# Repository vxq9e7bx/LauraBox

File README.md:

# LauraBox
A children's juke box controlled by RFID tags, based on an ESP32.

## Features:
* Playback of user-defined MP3 playlists
* Playlist selected though RFID tag. Cheap RFID stickers can be placed on any 3D printed model.
* Battery powered, can play while charging
* Four buttons: volume +/-, next/previous track
* Intuitive pause functionality by removing the RFID tag and putting it back on to resume (no limit in pause time, no impact on battery life)
* WiFi download of new MP3s and playlists
* Firmware upgrade via WiFi
* Long standby time (several month)
* Long play time (many hours, if not days)
* Toddler proof :-)

## Main components
* EPS32 microcontroller
* MFRC522 RFID board
* PCM5102 I2S stereo audio DAC
* PAM8403 stereo amplifier
* Pair of wideband speakers
* 3.6V Li-ion battery with USB charge controller from a USB power bank (2x 18650-type cells with 2500 mAh)
* SD card to store MP3 files and playlists

## Why use the ESP32?

At first I was considering building the box based on a Raspberry Pi. I had an old first generation Pi lying around unused, so I though it would be a good way of using it. I was immediately disappointed by its sound quality. Although this is significantly better on newer models, I learned another lession: The power consumption of a Raspberry Pi is very high, and it takes a long time to boot. Keeping it always running to wait for an RFID card to be detected is out of the question, since I wanted it to run from battery. Adding a small microcontroller (I though of some ATMega) to switch on the Pi only when a card is detected would result in long wait times until the music starts playing. Also the power consumption while playing would be still quite high. A Raspberry Pi typically uses 300 to 500 mA, while an ESP32 just takes a few mA when WiFi is disabled. After short investigation I found the ESP32-audioI2S Arduino library. This makes playback of audio using an ESP32 super easy. Thanks to the ultra low power co-processor of the ESP32 it is possible to cut down the power consumption in sleep mode to around 0.5mA-1.0mA on average (incl. periodic wakeups and RFID reads), which gives you plenty of standby time on battery.

## Power supply

For power supply I have used an old USB power bank which I no longer needed. It has two 18650-typed cells with each 2500 mAh and a USB charge controller with an integrated boost converted to generate 5V from the ~3.6 V battery voltage (the cells are in parallel). The 5V USB voltage is not usable to power a very low power device, since the boost converter switches off if too little current is drawn. Since the electronics anyways runs on 3.3 V, the battery voltage is used without the boost converter directly. Since the voltage can be as high as 4 V or even higher when the battery is fully chaged, and the ESP32 has a maximum voltage of 3.6 V, a voltage regulator is required. I have decided for a MaxLinear XRP6272, since it has a very low quiescent current, a quite low dropout voltage and is able to provide a high enough current so that WiFi will work without problems.

The PCM5102 has unfortunately a relatively high quiescent current, hence I decided to use two XRP6272: one for the ESP32, the MRF522 and the SD card, the second formt the PCM5102. The first regulator is permanently enabled, since the ESP32 needs permanent power, and both the SD card and the MRF522 can be powered down to a sufficiently low quiescent current. Only the second regulator is controlled by software.

The PAM8403 is directly connected to the battery voltage, since it is favourable to power it with the highest possible voltage (up to 5V). I have experimented with using the 5V USB power as a supply, but it draws too little current to switch it on. Luckily, the power down mode of the PAM8403 is also sufficiently low, so no extra switch is required here.

It is a bit difficult to measure the power consumption in standby mode precisely, because it switches between deep-sleep modes and very short bursts of RFID-activity (with only the ULP processor working in the ESP32). The average current seems to be around 1mA. Since the battery cannot be used to its full capacity, because the voltage is getting too low at some point, the lifetime is a bit below the theoretical 5000hours = 208days. Even if it were only half of that, it would be still nothing to worry about too much.

Also to get down the power consumption, I have removed the LED from the MFRC522 board. It was always on even while the MFRC522 was put to standby and hence was unnecessarily drawing a significant amount of power.

## Firmware

The firmware is based on Arduino and uses the following libraries:
* ESP32 I2S audio library: https://github.com/schreibfaul1/ESP32-audioI2S
* ArduinoOTA (from Arduino library manager)
* ArduinoHttpClient (from Arduino library manager)

It also uses the ulptool (https://github.com/duff2013/ulptool) to program the ULP (ultra low power co-processor) of the ESP32.

Please have a look at the header of the Arduino sketch for instructions how to build the firmware. You will also have to create the `wifi-key.h` header file containing your WiFi credentials and the URL to download MP3 and playlists from (see section "Server setup for playlists and MP3 files"):
```
// Create wifi-key.h, put the following two definitions in and replace the **** with your WIFI credentials.
String ssid =     "****";
String password = "****";
String updateCard = <cardIdToActivateWifiUpload>;
String baseUrl = "http://url.to.download.new.card.content"
```

The `<cardIdToActivateWifiUpload>` is the RFID card id (as an integer, prefix with `0x` for hex format) which will trigger entering the WiFi firmware update and playlist/MP3 download mode.

### Usage of the ULP

The ULP periodically queries the status of the RFID card, wakes the main CPU if a new card is detected, and informs the main CPU of the current card ID and when the card is lost. Writing this code was the actual fun part of the firmware development for this project. The ULP is a very minimalistic CPU, there isn't even a (complete) C compiler (I wasn't able to get the experimental ULPCC compiler to work at all). So I had to write assembler code. There are only very few registers. The CPU doesn't even have a stack, but you can implement one (see `stack.s`). Since the ULP does not have access to the peripherals (they are powered down anyway), the SPI communication with the MRFC522 has to be bit-banged through normal GPIO pins. To get this right, I have basically observed the communication of a normal Arduino program using an MRFC522 library with a logic analyzer. Then I have basically coded the same sequence of bytes into the ULP program (see `init_sequence` section in `rtcio.s`). The only goal was to read the ID of the card, which is luckily not so hard to achieve. Even though some error checking is missing, the communication seems to be pretty reliably.

Since the ULP can also run when the main CPU is active, it will keep monitoring the presence of the RFID card and inform the main CPU when it is lost. The main CPU will then shutdown. An interesting fact about the ESP32 is also that the main CPU will be completely shutoff while in deep sleep mode, so when the ULP wakes it, it will boot the program from the very beginning (i.e. it will go through `setup()` again). Only by looking at the wakeup cause it is possible to distinguish this from a cold boot. All memory content (apart from the ULP accessible memory) will be lost, too. For this particular purpose this is perfectly fine, since the box does not need to store big amount of data while sleeping. Only the current volume setting and the last playback position is stored in the ULP memory.

## Electronics

* Analogue part is well-separated from digital part, to avoid any influence of RFID or WiFi operation on sound quality.
* This works well, there is no audible noise from RFID or WiFi.

### Possible improvements:

* Some things may be a bit cheated: digital signals (I2S etc.) going to the analogue side should better be decoupled with opto-couplers, because ground levels might be different. It seems to work well like it is, though.
* Some components (choke, analogue supply bypass capacitor) are quite overdimensioned, just to be on the safe side.
  * I did that to avoid the risk of needing a second order with only a few parts, if I would estimate wrongly...
* Placement of some components was not smart:
  * The serial programming connector was originally planned as an upright connector, so it can be reached while the board is inside the box. This collided with the RFID board, so I changed it to an angled connector. This is a bit unhandy, because it requires taking the board out when using it. Also no big deal, since there is WiFi firmware upgarade...
  * Some bigger components, especially the choce, are placed a bit too close to the edge, which makes assembly a bit hard.
* Keep the area below the WiFi antenna free (no ground, no signals). This is hard to achieve with a home-produced board with just two layers, but at least one could move the signals as close as possible to the edge of the area and remove the ground plane there, ideally with a real cut out in the board.
* I am not an electronics engineer, surely one can do a number of other things better, too!

## Mechanical parts

* The outer parts are made from plywood with a CNC mill.
  * Don't look to close at my work. This was the first time for me do build such a case with my CNC mill, which is more like a 3D printer that can also mill...
* The buttons are also made from wood, which creates a uniform look. The reset button can be triggered with a paper clip.
* The wood is finished with wood wax.
* The holder for the battery and the charge controller are 3D printed.
* The corners holding the electronics have nuts glued in from the bottom.
* Spacers are required between the electronics and the top lid of the casing.
* Speakers are secured with screws and nuts. To simplify the assembly, I have glued the nuts to the speakers.

### Possible improvements:

* The drilled holes for the sound to exit the box are too small, this degrades sound quality a bit unfortunately.
* Assembly is slightly tedious due to the spacers between electronics and the lid, but thanks to Wifi connectivity this needs not be done often.
* Also the box is a bit too small for the electronics board (or the board is to big). I had to grind some material off the walls on the inside to make it fit.

## Server setup for playlists and MP3 files

* A web server needs to be setup which provides playlists and MP3 files
* The web server needs to be reachable by the box when connected to the WiFi defined in `wifi-key.h` through the specified URI.
  * It is strongly recommended to restrict access to the web server to your local network or even just the IP address of the box, to avoid exposing copyrighted material to the internet.
* When detecting the special `updateCard`, the firmware will download a file called `0.lst.manifest`, which contains a list of file sizes and names (one entry per line).
* It will then check each entry whether the file exists on the SD card and its size matches. Any missing or wrong-sized file will be downloaded. Any extra file will be deleted.
* Playlists need to be named after the card ID which should activate the play back of the list: `<cardId>.lst` (e.g. `deadbeef.lst` if `deadbeef` is a card id). They simply contain a plain list of MP3 files which should be played back in sequence. The playlist file and all MP3s need to be in the manifest file, so they are properly downloaded.
* During playback, there normally is no WiFi connection to safe power. It is possible though to have web radio streams in the playlists. If a playlist entry starts with `http://`, WiFi will be activated before the stream is started. Note that this will work only with MP3-based streams, and it will reduce the battery life considerably.
* To generate a playlist on a Linux system, use the script `scripts/makeList.sh`.
* To generate or update the manifest, use the script `scripts/makeManifest.sh`.
* Do not use non-ASCII characters in file names. Use the script `scripts/fileRenamer.sh` to rename files such that those characters are avoided.
* To correct the sound distortions caused by the small holes in the casing letting, I use the script `scripts/soundCorrection.sh`. I would recommend rather making those holes bigger, but if you face similar issues this can be helpful.
* If you have a Youtube Music account and want to download MP3 files from there to the box, have a look at the scripts `scripts/ytmSetup.py` and `scripts/ytmLoader.py` and modify them for your needs.

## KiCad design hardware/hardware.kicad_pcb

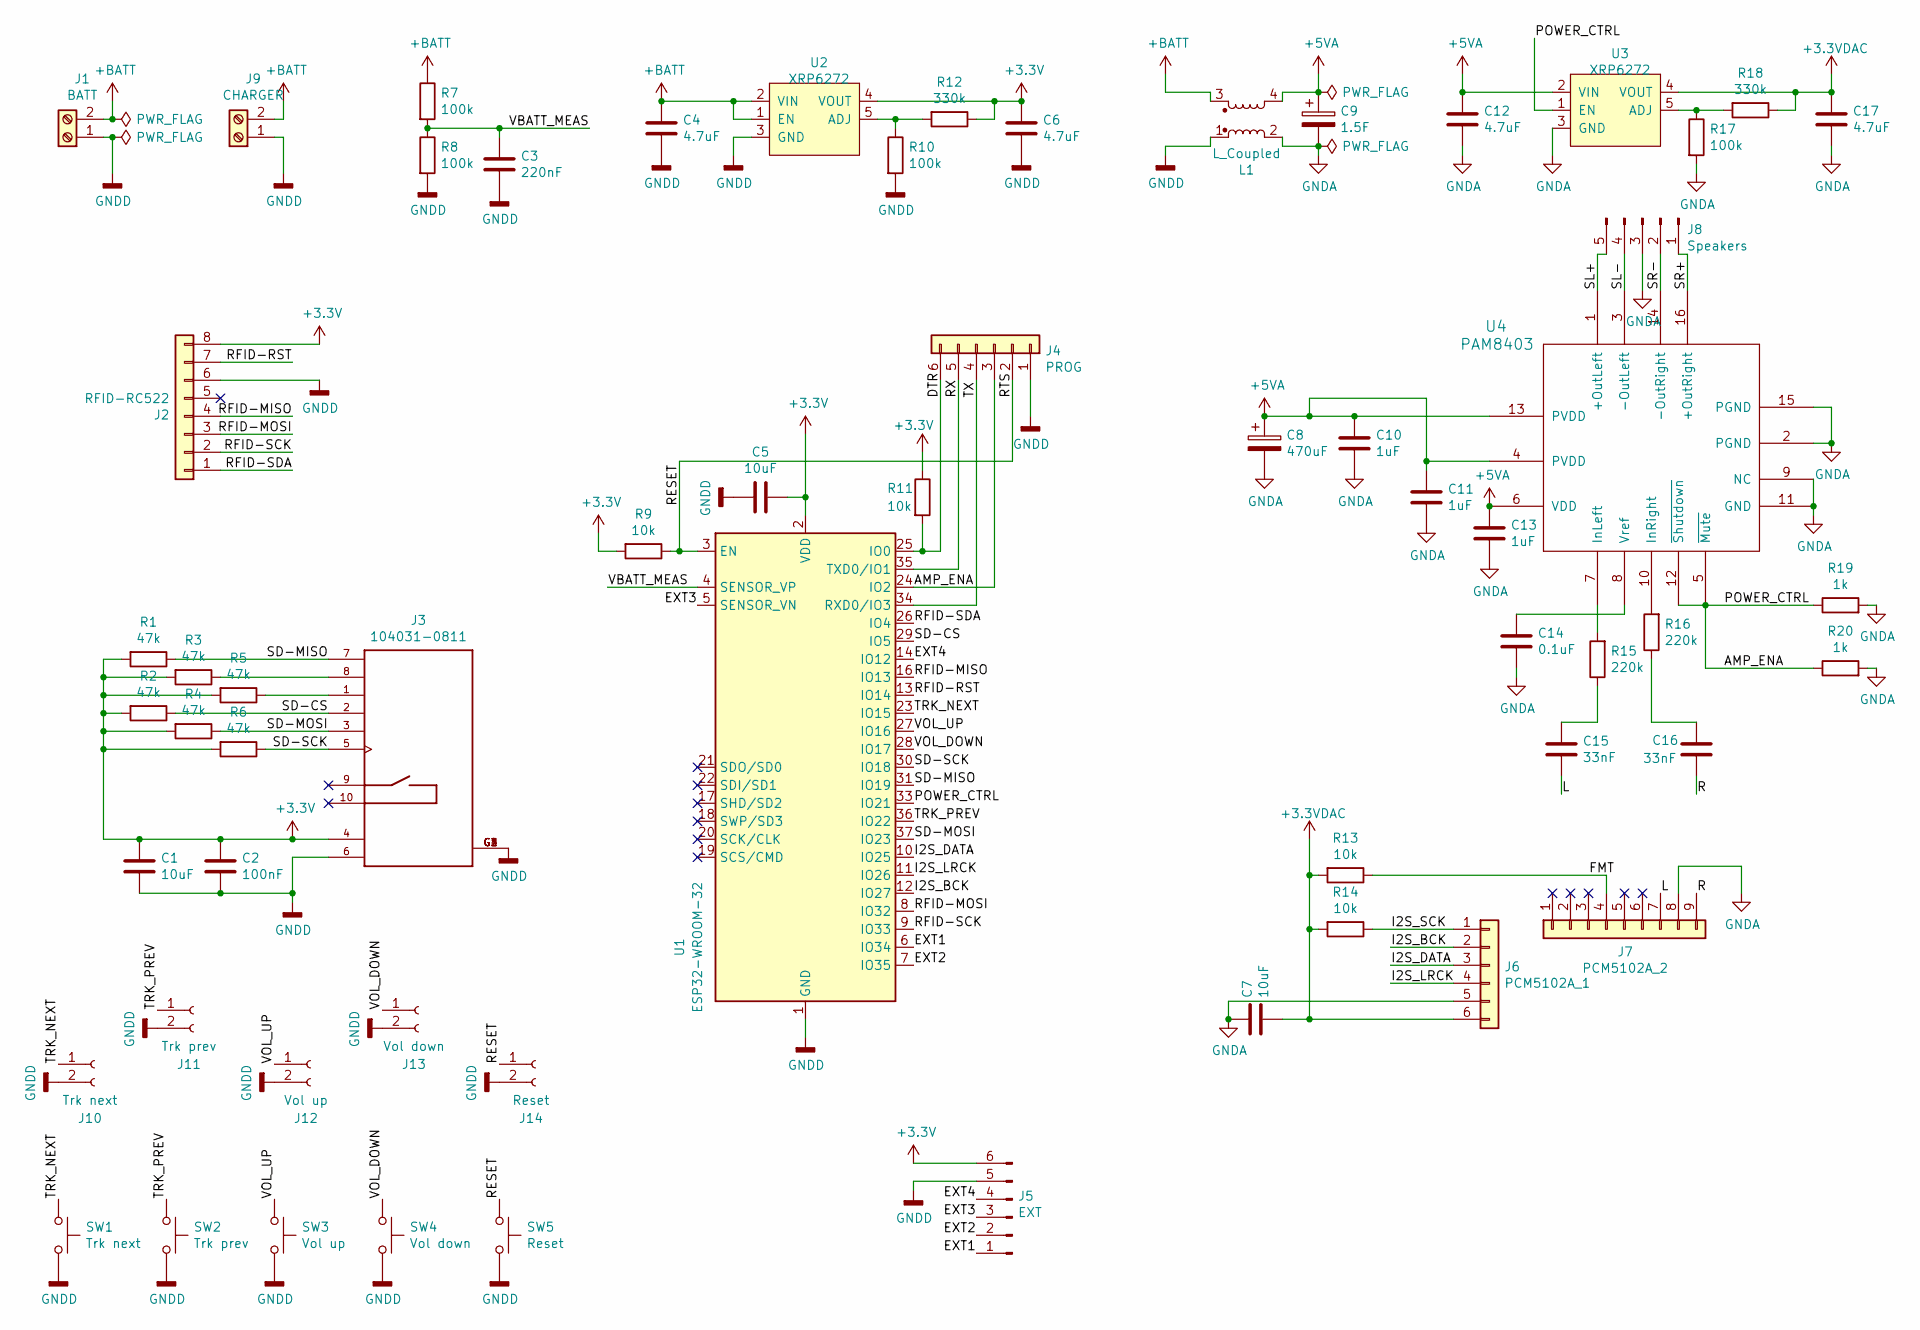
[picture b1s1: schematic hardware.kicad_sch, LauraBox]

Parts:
C1, C5, C7: 10uF; C_0805_2012Metric_Pad1.15x1.40mm_HandSolder
C2: 100nF; C_Disc_D3.0mm_W1.6mm_P2.50mm
C3: 220nF; C_Disc_D3.0mm_W1.6mm_P2.50mm
C4, C6, C12, C17: 4.7uF; C_1206_3216Metric_Pad1.42x1.75mm_HandSolder
C8: 470uF; CP_Radial_D8.0mm_P3.80mm
C9: 1.5F; C_Rect_L16.5mm_W8.7mm_P15.00mm_MKT
C10, C11, C13: 1uF; C_Rect_L4.6mm_W5.5mm_P2.50mm_MKS02_FKP02
C14: 0.1uF; C_Disc_D3.0mm_W1.6mm_P2.50mm
C15, C16: 33nF; C_Disc_D3.0mm_W1.6mm_P2.50mm
J1: BATT; Molex_KK-254_AE-6410-02A_1x02_P2.54mm_Vertical
J2: RFID-RC522; RFID-RC522-Module
J3: 104031-0811; 1040310811
J4: PROG; Molex_KK-254_AE-6410-06A_1x06_P2.54mm_Vertical
J5: EXT; PinHeader_2x03_P2.54mm_Vertical
J6: PCM5102A_1; PinSocket_1x06_P2.54mm_Vertical
J7: PCM5102A_2; PinSocket_1x09_P2.54mm_Vertical
J8: Speakers; Molex_KK-254_AE-6410-05A_1x05_P2.54mm_Vertical
J9: CHARGER; Molex_KK-254_AE-6410-02A_1x02_P2.54mm_Vertical
J10: Trk next; PinHeader_1x02_P2.54mm_Vertical
J11: Trk prev; PinHeader_1x02_P2.54mm_Vertical
J12: Vol up; PinHeader_1x02_P2.54mm_Vertical
J13: Vol down; PinHeader_1x02_P2.54mm_Vertical
J14: Reset; PinHeader_1x02_P2.54mm_Vertical
L1: L_Coupled; Choke_21x17mm
R1, R2, R3, R4, R5, R6: 47k; R_0612_1632Metric_Pad1.18x3.40mm_HandSolder
R7, R8, R10, R17: 100k; R_0612_1632Metric_Pad1.18x3.40mm_HandSolder
R9, R11, R13, R14: 10k; R_0612_1632Metric_Pad1.18x3.40mm_HandSolder
R12, R18: 330k; R_0612_1632Metric_Pad1.18x3.40mm_HandSolder
R15, R16: 220k; R_0612_1632Metric_Pad1.18x3.40mm_HandSolder
R19, R20: 1k; R_0612_1632Metric_Pad1.18x3.40mm_HandSolder
SW1: Trk next; SW_Push_1P1T_NO_6x6mm_H9.5mm
SW2: Trk prev; SW_Push_1P1T_NO_6x6mm_H9.5mm
SW3: Vol up; SW_Push_1P1T_NO_6x6mm_H9.5mm
SW4: Vol down; SW_Push_1P1T_NO_6x6mm_H9.5mm
SW5: Reset; SW_Push_1P1T_NO_6x6mm_H9.5mm
U1: ESP32-WROOM-32
U2, U3: XRP6272; TO-252-5_TabPin3
U4: PAM8403; SOP-16_4.55x10.3mm_P1.27mm

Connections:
+3.3VDAC: C7.2, C17.1, J6.6, R13.2, R14.2, R18.1, U3.4 (VOUT)
+3V3: C1.1, C2.1, C5.1, C6.1, J2.8, J3.4 (VDD), J5.6, R1.2, R2.2, R3.2, R4.2, R5.2, R6.2, R9.2, R11.1, R12.1, U1.2 (VDD), U2.4 (VOUT)
+5VA: C8.1, C9.1, C10.1, C11.1, C12.1, C13.1, L1.4, U3.2 (VIN), U4.4 (PVDD), U4.6 (VDD), U4.13 (PVDD)
+BATT: C4.1, J1.2, J9.2, L1.3, R7.1, U2.1 (EN), U2.2 (VIN)
/AMP_ENA: J4.3, R19.1, R20.1, U1.24 (IO2), U1.33 (IO21), U3.1 (EN), U4.5 (~Mute), U4.12 (~Shutdown)
/DTR: J4.6, R11.2, U1.25 (IO0)
/EXT1: J5.1, U1.6 (IO34)
/EXT2: J5.2, U1.7 (IO35)
/EXT3: J5.3, U1.5 (SENSOR_VN)
/EXT4: J5.4, U1.14 (IO12)
/FMT: J7.4, R13.1
/I2S_BCK: J6.2, U1.12 (IO27)
/I2S_DATA: J6.3, U1.10 (IO25)
/I2S_LRCK: J6.4, U1.11 (IO26)
/I2S_SCK: J6.1, R14.1
/L: C15.2, J7.7
/R: C16.1, J7.9
/RESET: J4.2, J14.1, R9.1, SW5.1, U1.3 (EN)
/RFID-MISO: J2.4, U1.16 (IO13)
/RFID-MOSI: J2.3, U1.8 (IO32)
/RFID-RST: J2.7, U1.13 (IO14)
/RFID-SCK: J2.2, U1.9 (IO33)
/RFID-SDA: J2.1, U1.26 (IO4)
/RX: J4.5, U1.35 (TXD0/IO1)
/SD-CS: J3.2 (CD/DAT3), R2.1, U1.29 (IO5)
/SD-MISO: J3.7 (DAT0), R1.1, U1.31 (IO19)
/SD-MOSI: J3.3 (CMD), R4.1, U1.37 (IO23)
/SD-SCK: J3.5 (CLK), R6.1, U1.30 (IO18)
/SL+: J8.5, U4.1 (+OutLeft)
/SL-: J8.4, U4.3 (-OutLeft)
/SR+: J8.1, U4.16 (+OutRight)
/SR-: J8.2, U4.14 (-OutRight)
/TRK_NEXT: J10.1, SW1.1, U1.23 (IO15)
/TRK_PREV: J11.1, SW2.1, U1.36 (IO22)
/TX: J4.4, U1.34 (RXD0/IO3)
/VBATT_MEAS: C3.1, R7.2, R8.1, U1.4 (SENSOR_VP)
/VOL_DOWN: J13.1, SW4.1, U1.28 (IO17)
/VOL_UP: J12.1, SW3.1, U1.27 (IO16)
GNDA: C7.1, C8.2, C9.2, C10.2, C11.2, C12.2, C13.2, C14.1, C17.2, J6.5, J7.8, J8.3, L1.2, R17.2, R19.2, R20.2, U3.3 (GND), U4.2 (PGND), U4.9 (NC), U4.11 (GND), U4.15 (PGND)
GNDD: C1.2, C2.2, C3.2, C4.2, C5.2, C6.2, J1.1, J2.6, J3.6 (VSS), J3.G1 (GND), J3.G2 (GND), J3.G3 (GND), J3.G4 (GND), J4.1, J5.5, J9.1, J10.2, J11.2, J12.2, J13.2, J14.2, L1.1, R8.2, R10.2, SW1.2, SW2.2, SW3.2, SW4.2, SW5.2, U1.1 (GND), U1.15 (GND), U1.38 (GND), U1.39 (GND), U2.3 (GND)
unnamed: C14.2, U4.8 (Vref)
unnamed: C15.1, R15.1
unnamed: C16.2, R16.1
unnamed: J3.1 (DAT2), R5.1
unnamed: J3.8 (DAT1), R3.1
unnamed: R10.1, R12.2, U2.5 (ADJ)
unnamed: R15.2, U4.7 (InLeft)
unnamed: R16.2, U4.10 (InRight)
unnamed: R17.1, R18.2, U3.5 (ADJ)

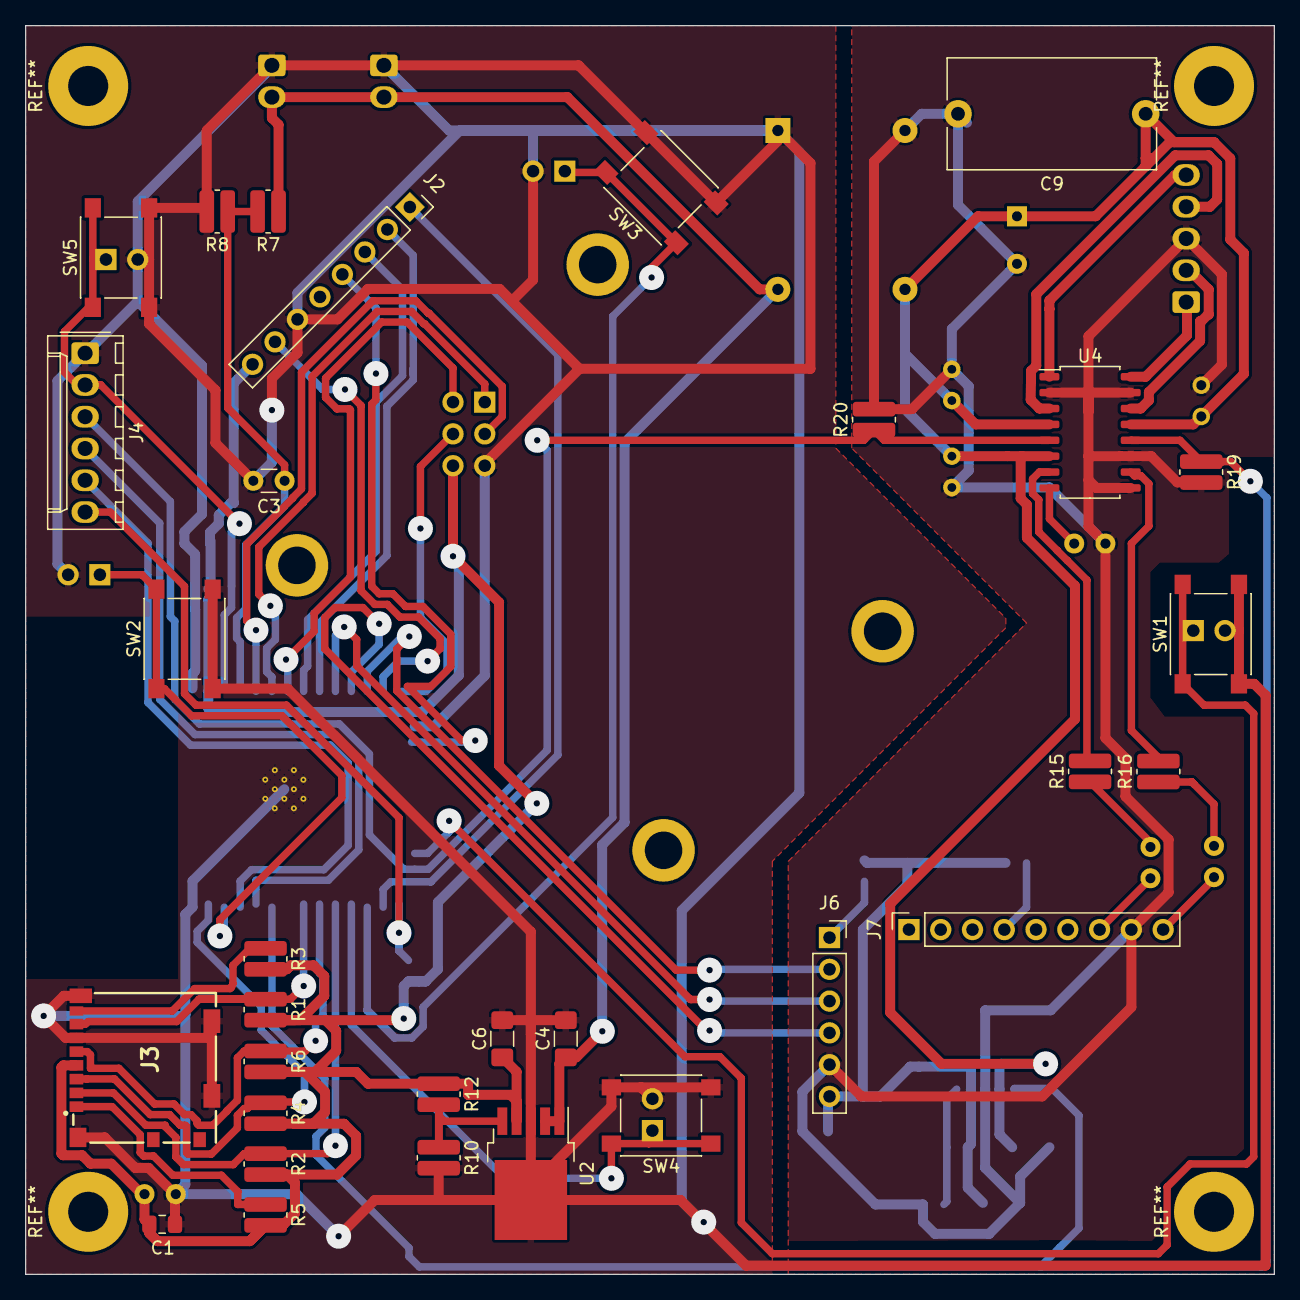
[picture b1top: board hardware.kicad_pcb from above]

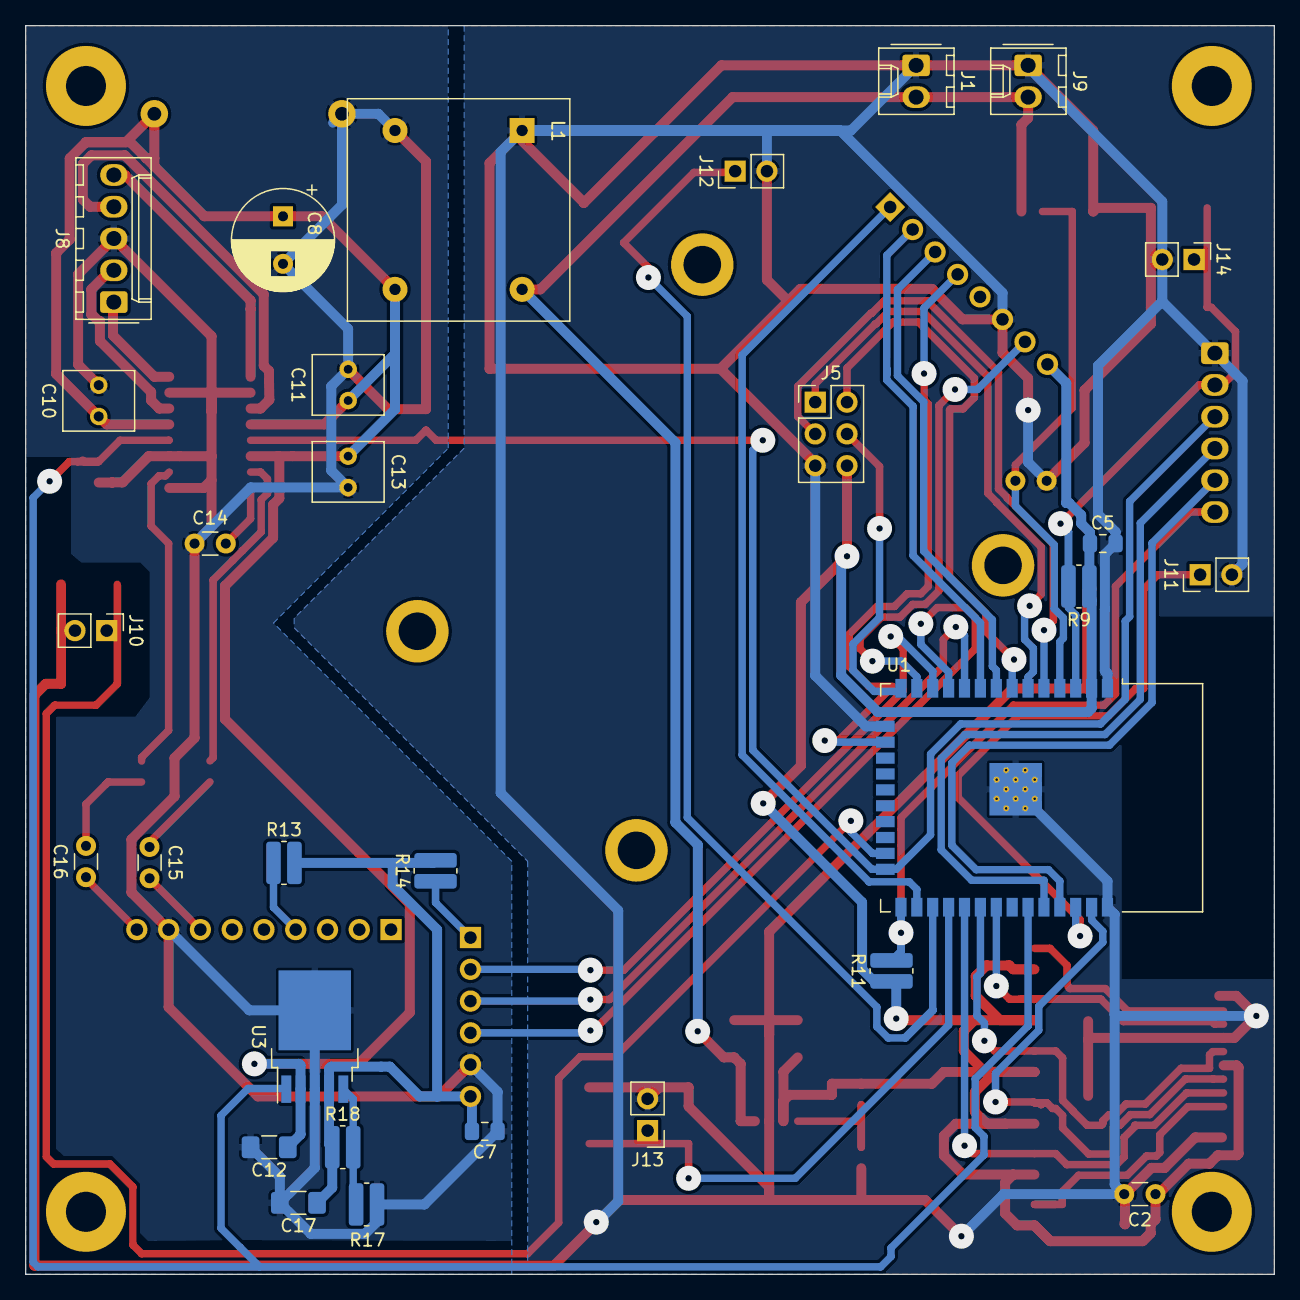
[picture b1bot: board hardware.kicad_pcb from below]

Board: 2 copper layers, 99.8 x 99.8 mm, 61 parts (30 on the bottom side), 49 nets.

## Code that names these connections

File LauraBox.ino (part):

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
// Pins for I2S audio interface
#define I2S_DOUT      25
#define I2S_SCK       27
#define I2S_LRCK      26

// Pin for power control (DAC and amplifier)
#define POWER_CTRL    21

// Pin for amplifier /shutdown and /mute signals
#define AMP_ENA       2   // needs to be pulled low for fw download -> put to programmer connector to be safe

// ADC channel to read the battery voltage. Keep in sync with constant in rtcio.s
#define ADC_CH_VBATT ADC1_CHANNEL_0
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  // configure power control pin
  Serial.printf("Power on SD+Audio\n");
  pinMode(POWER_CTRL, OUTPUT);
  pinMode(AMP_ENA, OUTPUT);
  digitalWrite(AMP_ENA, LOW);
  digitalWrite(POWER_CTRL, HIGH);

  // Configure audo interface
  Serial.printf("Setup audio\n");
  audio.setPinout(I2S_SCK, I2S_LRCK, I2S_DOUT);

  // create task for audio loop (on a dedicated core)
  std::lock_guard<std::recursive_mutex> lk(mx_audio);   // prevent audio loop until setup is complete
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
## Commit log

2020-03-14 some first attempts, not yet working
2020-03-14 some cleanup
2020-03-14 import MRFC522 library from https://github.com/ljos/MFRC522
2020-03-14 get SD card and RFID scanner to work at the same time
    by moving the RFID scanner to the other SPI port
2020-03-14 play back playlist depending on card ID
2020-03-15 introduce volume buttons, simplify code for playlist advance
2020-03-15 wip: schematics
2020-03-17 wip: power supply
2020-03-18 wip: power switch and cleanup
2020-03-20 fix power switch circuit
2020-03-22 added test code for low power microcontroller
2020-03-23 configure unused pins as INPUT_PULLUP
2020-03-23 wip: power measurement documentation
2020-03-23 corrected formatting
2020-03-23 more formatting
2020-03-23 formatting...
2020-03-23 completed power estimation
2020-03-29 wip: use ULP for MFRC522 communcation (+ some code cleaning and experiments)
2020-03-31 wip: rfid card readout via ULP coprocessor. card detection works now.
2020-04-01 detect card uid in ULP coprocessor and send it to main processor
2020-04-01 remove an unncessary command
2020-04-06 wakeup only when new card is detected, and some code cleaning
2020-04-07 implement playback logic, needs testing
2020-04-07 update schematics
2020-04-07 added cache library to repo
2020-04-07 added kicad cache and backup files to gitignore
2020-04-17 update schematics, improve power distribution concept
2020-04-22 some fixes to the schematics
2020-04-25 use spinlock to make card id transfer from ulp to main cpu atomic
2020-04-26 change pin assignment to avoid strapping pins
2020-04-26 change default volume
2020-04-26 fix spin lock for atomic card id exchange
2020-04-26 fix ULP hanging after resume playback
2020-04-26 improve debug output
2020-04-26 only read card id from ULP once per loop iteration
2020-04-26 reset paused flag on resume
2020-04-26 run audio loop while waiting for spinlock
2020-04-26 clear i2s buffer when pausing to avoid clicking noise
2020-04-26 rename NFC SS pin into SDA for consistency
2020-04-26 update schematics for changed pin assignment
2020-04-26 fix signal names for I2S, and wrong wiring
2020-05-12 some fixes and add ADC measurement for battery voltage
2020-05-15 use external library for ESP32-audioI2S, add voice messages to SPIFFS
2020-05-15 some corrections about the voice error
2020-05-19 pause with deep sleep for unlimited time; allow web streaming
2020-05-19 correction: amplifier has separate pin for enable
2020-05-24 minor correction
2020-05-24 Reduce coupling capacitor between DAC and amplifier
    This is necessary to reduce the pop noise when switching on. The corner frequency is still much lower than the bandwidth of the speakers.
2020-05-24 fix ERC errors, separate AMP_UNMUTE from AMP_ENA
2020-05-24 fix missing annotation
2020-05-24 fix name of EXT header
2020-05-24 layout corrections
2020-05-24 use POWER_CTRL to shutdown the amp, AMP_ENA to mute it
2020-05-24 add reset button
2020-05-24 reduce standby power consumption
2020-06-04 fixed annotation
2020-06-05 assign footprints, generate netlist
2020-06-05 fix footprint for choke
2020-06-05 update gitignore
2020-06-11 [wip] board layout
2020-06-20 [wip] routing...
2020-06-21 PBC routing complete
2020-08-30 corrections to PCB, started 3D model
2020-08-31 added 3D models for electronic subcomponents
2020-08-31 added 3D model for main board with subcomponents
2020-09-07 finalize 3D model
2020-09-07 finalize PCB
2020-09-07 create milling files for PCB
2020-09-07 update flatcam project
2020-09-19 update 3D model and PCB
2020-09-25 fix 3D model (wrong material thickness)
2020-09-29 updated model
2020-10-04 add Wifi firmware updated
2020-10-04 final model update
2020-10-05 wip: auto-download playlists from local web server
2020-10-05 intermediate commit
2020-10-05 added youtube music loader scripts
2020-10-10 fix auto-download of audio files
2020-10-10 extend scripts
2020-10-10 update sound correction script
2020-10-10 more fixes for auto download of tracks
2020-10-10 remove unnecessary sleep
2020-10-11 fix not advancing to next track, improve status messages when downloading
2020-10-11 some fixes and improvements
2020-10-11 more fixes
2021-01-04 add comment how to install dependencies
2021-01-04 fix file modes
2021-01-04 add script to create manitfest files
2021-01-04 fix file modes, update makeManifest
2021-01-04 replace automatic download of playlists in the background by triggered download through magic card ID
2021-01-04 disable button auto-repeat
2021-01-04 fix for new Linux versions
2021-01-06 add base plate files
2021-01-07 add script to create play lists
2021-01-26 add images
2021-01-27 add schematics as SVG
2021-01-27 add title and estimated date
2021-01-27 remove outdated and unused code
2021-01-28 update comment
2021-10-01 sound correction script: allow do adjust volume
2021-10-01 ytmLoader script: allow to specify playlist on command line
2021-10-01 update of model
2021-10-02 fix missing leading zeros in card id
2022-11-13 adjustments: reroute tracks to keep-out antenna add optional pin headers below/close to buttons for external push buttons minor cleanup
2022-11-13 kosmetik
2022-11-19 httpCode cannot be <200 and >299 at the same time...
